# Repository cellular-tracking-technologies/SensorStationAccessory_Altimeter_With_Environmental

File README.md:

# SensorStation Accessory: Altimeter with Environmental Monitoring

This SensorStation accessory features the Bosch BME680, allowing you to monitor your local environment! The accessory also allows
you to calibrate the altimeters of wildlife telemetry devices.

The BME680 is an integrated environmental sensor that provides the following:

* Pressure (altimeter grade)
* Temperature
* Humidity
* Gas sensing (VOC's)

When used with a properly vented encosure, you can use SensorStation to monitor the weather as well as air quality.

When used inside a tight, waterproof enclosure, the BME680 can provide additional clues on the health of your SensorStation. For example:

Increasing humidity would indicate a leak of your waterproof case, connections, or other water hazards that could damage your SensorStation

High temperature conditions may indicate more cooling is needed, or the enclosure should be relocated to the shade

Gas sensing could indicate a future problem with an electronic component or potential battery failure

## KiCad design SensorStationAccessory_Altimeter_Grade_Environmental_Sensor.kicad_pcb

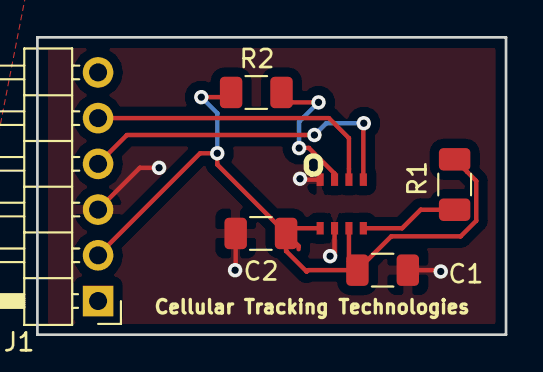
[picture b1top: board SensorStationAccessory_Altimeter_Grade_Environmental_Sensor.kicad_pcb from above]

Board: 2 copper layers, 26.0 x 16.5 mm, 6 parts (0 on the bottom side), 6 nets.

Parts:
C1, C2: 100n; C_1206_3216Metric
J1: SensorStation Accessory Plug; PinHeader_1x06_P2.54mm_Horizontal
R1, R2: 10K; R_1206_3216Metric
U1: BME680

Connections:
+3V3: C1.1, C2.1, J1.2, R1.1, R2.1, U1.6, U1.8
GND: C1.2, C2.2, J1.3, U1.1, U1.7
unnamed: R1.2, U1.5
unnamed: R2.2, U1.2
SCL: J1.4, U1.4
SDA: J1.5, U1.3

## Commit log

2019-07-24 Adding final design to github
2019-07-24 Made filenames more reasonable
